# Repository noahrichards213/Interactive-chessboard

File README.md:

# Interactive chessboard

LED-Guided Smart Chessboard
An interactive, LED-guided smart chessboard designed for beginners. The board uses magnetic piece tracking via Hall effect sensors and provides real-time visual move guidance through an integrated LED matrix, all run by an ESP32.

# How it works:
All the chess pieces have small magnets taped on the bottom
On each square of the chessboard, there is a Hall effect sensor, which detects if a square is occupied or empty. 
So, we  calculate piece movement by polling the Hall effects twice:
1. If a Hall effect has changed from detecting something to not detecting something, then a piece has been lifted up
2. Then, if a Hall effect has changed from not detecting something to detecting something, then that piece has been placed down

As such, we have information about the location of all the pieces on the board on every move, which is stored in an 8x8 array.
From there, we iterate over every piece and run an algorithm to update its legal moves. These algorithms take advantage of the geometry of the chessboard. For example, a rook can move horizontally and vertically, so the algorithm to check rook moves checks elements in the array that are in the same row or column. 

Each square on the board is assigned a number, and the available moves of each piece are stored in an array containing these numbers. The number uniquely encodes information about the row and column of the square. The array exists as a field in the Piece object.

The numbers in that array are mapped to a 64-bit binary number that indicates which LED should be lit up. 
For example, the number 25 corresponds to the square with row 2 and column 5 (0-indexed). Each shift register controls the LEDS in a particular row, so the number 2 indicates which register ought to receive data, and the number 5 indicates which of the pins on that shift register ought to receive data. The data in question is the bit 0. The pins of the shift register are connected to the negative terminal of the LEDs. Since the positive end of the LED is always powered, upon receiving a bit 0, the LED is grounded and will light up. Otherwise, the LED is not connected and will not light up.

We iterate this algorithm over all the available moves for a piece that has been lifted up, so the player can see which moves exist in the position.
Upon checkmate, a similar algorithm is used to light up:
1. the checkmated king
2. the enemy pieces that contributed to the checkmate

Video of the Scholar's mate:

https://github.com/user-attachments/assets/231e7ca0-4020-4f57-ace3-88c942b9550d

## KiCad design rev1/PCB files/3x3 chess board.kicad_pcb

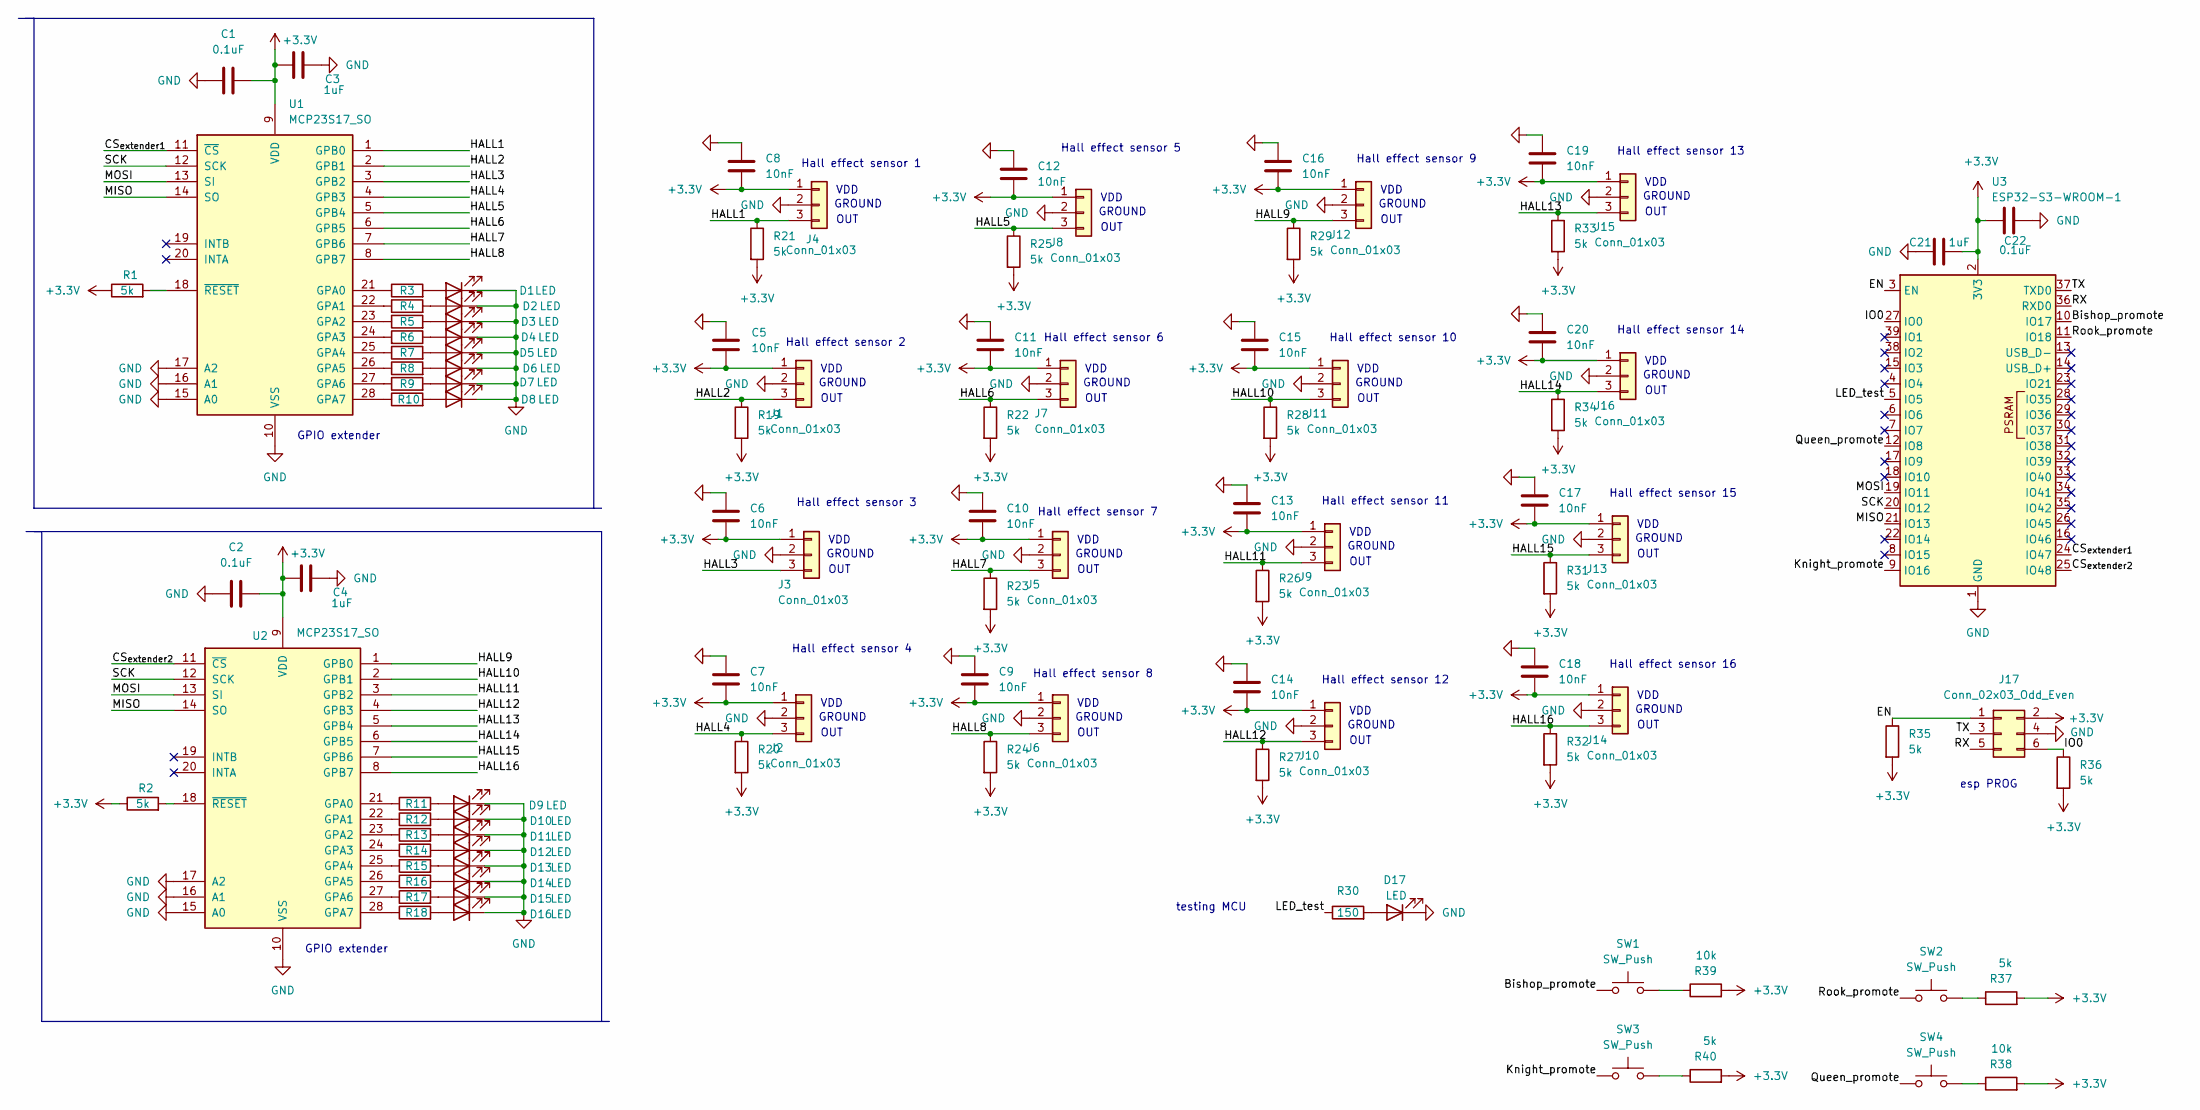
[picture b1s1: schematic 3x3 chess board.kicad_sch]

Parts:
C1, C2, C22: 0.1uF; C_0805_2012Metric
C3, C4, C21: 1uF; C_0805_2012Metric
C5, C6, C7, C8, C9, C10, C11, C12, C13, C14, C15, C16, C17, C18, C19, C20: 10nF; C_0805_2012Metric
D1, D2, D3, D4, D5, D6, D7, D8, D9, D10, D11, D12, D13, D14, D15, D16, D17: LED; D_0805_2012Metric_Pad1.15x1.40mm_HandSolder
J1, J2, J3, J4, J5, J6, J7, J8, J9, J10, J11, J12, J13, J14, J15, J16: Conn_01x03; TSOT-3L_MLX92232LSE-AAA-002-SP_MEL
J17: Conn_02x03_Odd_Even; IDC-Header_2x03_P2.54mm_Vertical
R1, R2, R19, R20, R21, R22, R23, R24, R25, R26, R27, R28, R29, R31, R32, R33, R34, R35, R36, R37, R40: 5k; R_0805_2012Metric_Pad1.20x1.40mm_HandSolder
R3, R4, R5, R6, R7, R8, R9, R10, R11, R12, R13, R14, R15, R16, R17, R18, R30: 150; R_0805_2012Metric_Pad1.20x1.40mm_HandSolder
R38, R39: 10k; R_0805_2012Metric_Pad1.20x1.40mm_HandSolder
SW1, SW2, SW3, SW4: SW_Push; SW_PUSH_6mm_H4.3mm
U1, U2: MCP23S17_SO; SOIC-28W_7.5x17.9mm_P1.27mm
U3: ESP32-S3-WROOM-1

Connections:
+3.3V: C1.2, C2.2, C3.2, C4.2, C5.2, C6.2, C7.2, C8.2, C9.2, C10.2, C11.2, C12.2, C13.2, C14.2, C15.2, C16.2, C17.2, C18.2, C19.2, C20.2, C21.2, C22.2, J1.1, J2.1, J3.1, J4.1, J5.1, J6.1, J7.1, J8.1, J9.1, J10.1, J11.1, J12.1, J13.1, J14.1, J15.1, J16.1, J17.2, R1.1, R2.1, R19.2, R20.2, R21.2, R22.2, R23.2, R24.2, R25.2, R26.2, R27.2, R28.2, R29.2, R31.2, R32.2, R33.2, R34.2, R35.2, R36.2, R37.2, R38.2, R39.2, R40.2, U1.9 (VDD), U2.9 (VDD), U3.2 (3V3)
/Bishop_promote: SW1.1, U3.10 (IO17)
/CS_{extender1}: U1.11 (~CS), U3.24 (IO47)
/CS_{extender2}: U2.11 (~CS), U3.25 (IO48)
/EN: J17.1, R35.1, U3.3 (EN)
/HALL1: J4.3, R21.1, U1.1 (GPB0)
/HALL2: J1.3, R19.1, U1.2 (GPB1)
/HALL3: J3.3, U1.3 (GPB2)
/HALL4: J2.3, R20.1, U1.4 (GPB3)
/HALL5: J8.3, R25.1, U1.5 (GPB4)
/HALL6: J7.3, R22.1, U1.6 (GPB5)
/HALL7: J5.3, R23.1, U1.7 (GPB6)
/HALL8: J6.3, R24.1, U1.8 (GPB7)
/HALL9: J12.3, R29.1, U2.1 (GPB0)
/HALL10: J11.3, R28.1, U2.2 (GPB1)
/HALL11: J9.3, R26.1, U2.3 (GPB2)
/HALL12: J10.3, R27.1, U2.4 (GPB3)
/HALL13: J15.3, R33.1, U2.5 (GPB4)
/HALL14: J16.3, R34.1, U2.6 (GPB5)
/HALL15: J13.3, R31.1, U2.7 (GPB6)
/HALL16: J14.3, R32.1, U2.8 (GPB7)
/IO0: J17.6, R36.1, U3.27 (IO0)
/Knight_promote: SW3.1, U3.9 (IO16)
/LED_test: R30.1, U3.5 (IO5)
/MISO: U1.14 (SO), U2.14 (SO), U3.21 (IO13)
/MOSI: U1.13 (SI), U2.13 (SI), U3.19 (IO11)
/Queen_promote: SW4.1, U3.12 (IO8)
/RX: J17.5, U3.36 (RXD0)
/Rook_promote: SW2.1, U3.11 (IO18)
/SCK: U1.12 (SCK), U2.12 (SCK), U3.20 (IO12)
/TX: J17.3, U3.37 (TXD0)
GND: C1.1, C2.1, C3.1, C4.1, C5.1, C6.1, C7.1, C8.1, C9.1, C10.1, C11.1, C12.1, C13.1, C14.1, C15.1, C16.1, C17.1, C18.1, C19.1, C20.1, C21.1, C22.1, D1.1 (K), D2.1 (K), D3.1 (K), D4.1 (K), D5.1 (K), D6.1 (K), D7.1 (K), D8.1 (K), D9.1 (K), D10.1 (K), D11.1 (K), D12.1 (K), D13.1 (K), D14.1 (K), D15.1 (K), D16.1 (K), D17.1 (K), J1.2, J2.2, J3.2, J4.2, J5.2, J6.2, J7.2, J8.2, J9.2, J10.2, J11.2, J12.2, J13.2, J14.2, J15.2, J16.2, J17.4, U1.10 (VSS), U1.15 (A0), U1.16 (A1), U1.17 (A2), U2.10 (VSS), U2.15 (A0), U2.16 (A1), U2.17 (A2), U3.1 (GND), U3.40 (GND), U3.41 (GND)
unnamed: D1.2 (A), R3.2
unnamed: D2.2 (A), R4.2
unnamed: D3.2 (A), R5.2
unnamed: D4.2 (A), R6.1
unnamed: D5.2 (A), R7.2
unnamed: D6.2 (A), R8.2
unnamed: D7.2 (A), R9.2
unnamed: D8.2 (A), R10.2
unnamed: D9.2 (A), R11.2
unnamed: D10.2 (A), R12.2
unnamed: D11.2 (A), R13.2
unnamed: D12.2 (A), R14.2
unnamed: D13.2 (A), R15.2
unnamed: D14.2 (A), R16.2
unnamed: D15.2 (A), R17.2
unnamed: D16.2 (A), R18.2
unnamed: D17.2 (A), R30.2
unnamed: R37.1, SW2.2
unnamed: R38.1, SW4.2
unnamed: R39.1, SW1.2
unnamed: R40.1, SW3.2
unnamed: R3.1, U1.21 (GPA0)
unnamed: R4.1, U1.22 (GPA1)
unnamed: R5.1, U1.23 (GPA2)
unnamed: R6.2, U1.24 (GPA3)
unnamed: R7.1, U1.25 (GPA4)
unnamed: R8.1, U1.26 (GPA5)
unnamed: R9.1, U1.27 (GPA6)
unnamed: R10.1, U1.28 (GPA7)
unnamed: R1.2, U1.18 (~RESET)
unnamed: R11.1, U2.21 (GPA0)
unnamed: R12.1, U2.22 (GPA1)
unnamed: R13.1, U2.23 (GPA2)
unnamed: R14.1, U2.24 (GPA3)
unnamed: R15.1, U2.25 (GPA4)
unnamed: R16.1, U2.26 (GPA5)
unnamed: R17.1, U2.27 (GPA6)
unnamed: R18.1, U2.28 (GPA7)
unnamed: R2.2, U2.18 (~RESET)

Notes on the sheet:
GROUND
testing MCU
VDD
Hall effect sensor 6
OUT
GPIO extender
Hall effect sensor 7
Hall effect sensor 15
Hall effect sensor 5
Hall effect sensor 10
esp PROG
Hall effect sensor 13
Hall effect sensor 11
Hall effect sensor 14
Hall effect sensor 16
Hall effect sensor 12
Hall effect sensor 3
Hall effect sensor 1
Hall effect sensor 9
Hall effect sensor 4
Hall effect sensor 8
Hall effect sensor 2

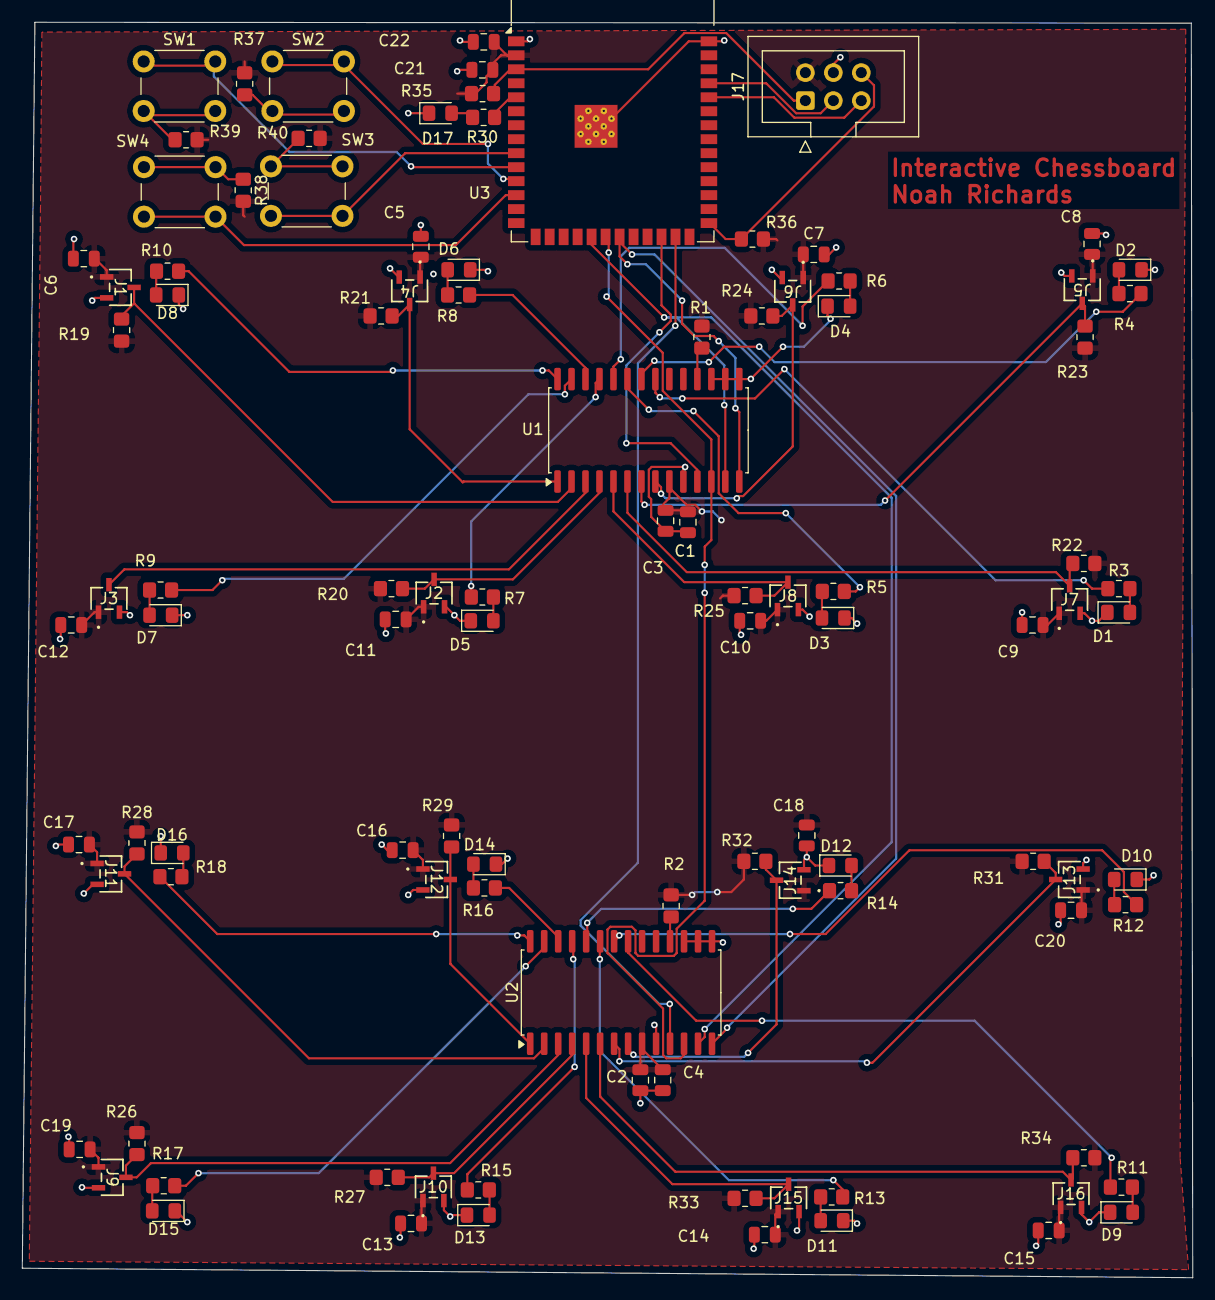
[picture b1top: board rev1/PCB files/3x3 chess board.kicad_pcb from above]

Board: 2 copper layers, 106.3 x 114.0 mm, 103 parts (0 on the bottom side), 71 nets.

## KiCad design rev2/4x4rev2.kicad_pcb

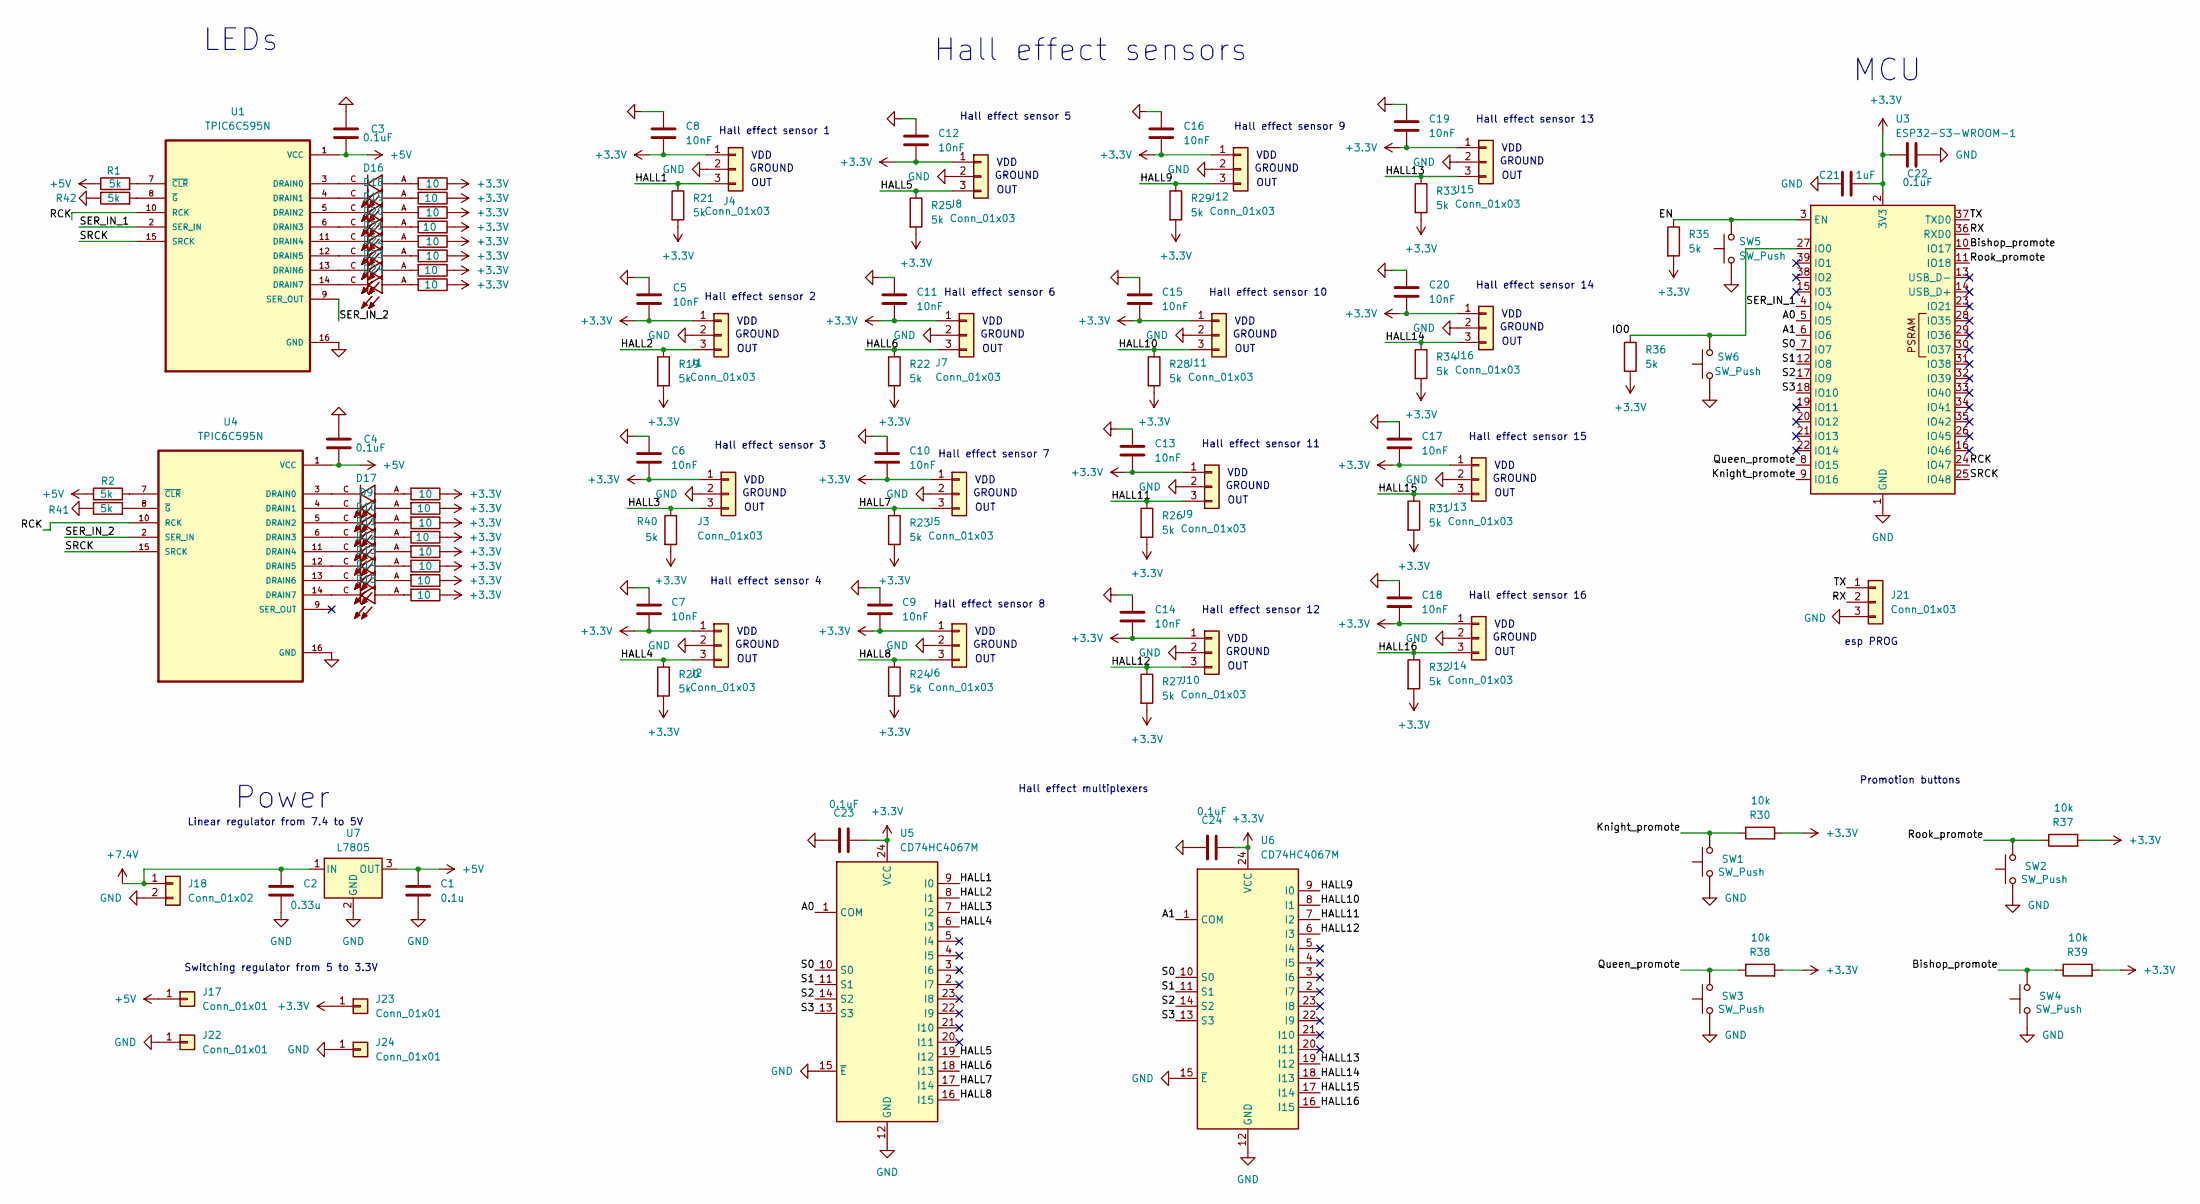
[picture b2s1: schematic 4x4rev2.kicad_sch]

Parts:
C1: 0.1u; C_0805_2012Metric
C2: 0.33u; C_0805_2012Metric
C3, C4, C22, C23, C24: 0.1uF; C_0805_2012Metric
C5, C6, C7, C8, C9, C10, C11, C12, C13, C14, C15, C16, C17, C18, C19, C20: 10nF; C_0805_2012Metric
C21: 1uF; C_0805_2012Metric
D9, D10, D11, D12, D13, D14, D15, D16, D17, D18, D19, D20, D21, D22, D23, D24: JB5630AWT-P-H40GA0000-NZ000001; LED_JB5630AWT-P-H40GA0000-NZ000001; PARTREV 3
J1, J2, J3, J4, J5, J6, J7, J8, J9, J10, J11, J12, J13, J14, J15, J16: Conn_01x03; TSOT-3L_MLX92232LSE-AAA-002-SP_MEL
J17, J22, J23, J24: Conn_01x01; PinHeader_1x01_P2.54mm_Vertical
J18: Conn_01x02; AMASS_XT30U-M_1x02_P5.0mm_Vertical
J21: Conn_01x03; PinHeader_1x03_P2.54mm_Vertical
R1, R2, R19, R20, R21, R22, R23, R24, R25, R26, R27, R28, R29, R31, R32, R33, R34, R35, R36, R40, R41, R42: 5k; R_0805_2012Metric_Pad1.20x1.40mm_HandSolder
R3, R4, R5, R6, R7, R8, R9, R10, R11, R12, R13, R14, R15, R16, R17, R18: 10; R_0805_2012Metric_Pad1.20x1.40mm_HandSolder
R30, R37, R38, R39: 10k; R_0805_2012Metric_Pad1.20x1.40mm_HandSolder
SW1, SW2, SW3, SW4, SW5, SW6: SW_Push; SW_SPST_SKQG_WithStem
U1, U4: TPIC6C595N; SOIC127P600X175-16N
U3: ESP32-S3-WROOM-1
U5, U6: CD74HC4067M; SOIC127P1030X265-24N
U7: L7805; L7805CDTTR

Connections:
+3.3V: C5.2, C6.2, C7.2, C8.2, C9.2, C10.2, C11.2, C12.2, C13.2, C14.2, C15.2, C16.2, C17.2, C18.2, C19.2, C20.2, C21.2, C22.2, C23.2, C24.2, J1.1, J2.1, J3.1, J4.1, J5.1, J6.1, J7.1, J8.1, J9.1, J10.1, J11.1, J12.1, J13.1, J14.1, J15.1, J16.1, J23.1, R3.1, R4.1, R5.1, R6.1, R7.1, R8.1, R9.1, R10.1, R11.1, R12.1, R13.1, R14.1, R15.1, R16.1, R17.1, R18.1, R19.2, R20.2, R21.2, R22.2, R23.2, R24.2, R25.2, R26.2, R27.2, R28.2, R29.2, R30.2, R31.2, R32.2, R33.2, R34.2, R35.2, R36.2, R37.2, R38.2, R39.2, R40.2, U3.2 (3V3), U5.24 (VCC), U6.24 (VCC)
+5V: C1.1, C3.2, C4.2, J17.1, R1.1, R2.1, U1.1 (VCC), U4.1 (VCC), U7.3 (OUT)
+7.4V: C2.1, J18.1, U7.1 (IN)
/A0: U3.5 (IO5), U5.1 (COM)
/A1: U3.6 (IO6), U6.1 (COM)
/Bishop_promote: R39.1, SW4.2, U3.10 (IO17)
/EN: R35.1, SW5.2, U3.3 (EN)
/HALL1: J4.3, R21.1, U5.9 (I0)
/HALL2: J1.3, R19.1, U5.8 (I1)
/HALL3: J3.3, R40.1, U5.7 (I2)
/HALL4: J2.3, R20.1, U5.6 (I3)
/HALL5: J8.3, R25.1, U5.19 (I12)
/HALL6: J7.3, R22.1, U5.18 (I13)
/HALL7: J5.3, R23.1, U5.17 (I14)
/HALL8: J6.3, R24.1, U5.16 (I15)
/HALL9: J12.3, R29.1, U6.9 (I0)
/HALL10: J11.3, R28.1, U6.8 (I1)
/HALL11: J9.3, R26.1, U6.7 (I2)
/HALL12: J10.3, R27.1, U6.6 (I3)
/HALL13: J15.3, R33.1, U6.19 (I12)
/HALL14: J16.3, R34.1, U6.18 (I13)
/HALL15: J13.3, R31.1, U6.17 (I14)
/HALL16: J14.3, R32.1, U6.16 (I15)
/IO0: R36.1, SW6.2, U3.27 (IO0)
/Knight_promote: R30.1, SW1.2, U3.9 (IO16)
/Queen_promote: R38.1, SW3.2, U3.8 (IO15)
/RCK: U1.10 (RCK), U3.24 (IO47), U4.10 (RCK)
/RX: J21.2, U3.36 (RXD0)
/Rook_promote: R37.1, SW2.2, U3.11 (IO18)
/S0: U3.7 (IO7), U5.10 (S0), U6.10 (S0)
/S1: U3.12 (IO8), U5.11 (S1), U6.11 (S1)
/S2: U3.17 (IO9), U5.14 (S2), U6.14 (S2)
/S3: U3.18 (IO10), U5.13 (S3), U6.13 (S3)
/SER_IN_1: U1.2 (SER_IN), U3.4 (IO4)
/SER_IN_2: U1.9 (SER_OUT), U4.2 (SER_IN)
/SRCK: U1.15 (SRCK), U3.25 (IO48), U4.15 (SRCK)
/TX: J21.1, U3.37 (TXD0)
GND: C1.2, C2.2, C3.1, C4.1, C5.1, C6.1, C7.1, C8.1, C9.1, C10.1, C11.1, C12.1, C13.1, C14.1, C15.1, C16.1, C17.1, C18.1, C19.1, C20.1, C21.1, C22.1, C23.1, C24.1, J1.2, J2.2, J3.2, J4.2, J5.2, J6.2, J7.2, J8.2, J9.2, J10.2, J11.2, J12.2, J13.2, J14.2, J15.2, J16.2, J18.2, J21.3, J22.1, J24.1, R41.1, R42.1, SW1.1, SW2.1, SW3.1, SW4.1, SW5.1, SW6.1, U1.16 (GND), U3.1 (GND), U3.40 (GND), U3.41 (GND), U4.16 (GND), U5.12 (GND), U5.15 (~E), U6.12 (GND), U6.15 (~E), U7.2 (GND)
unnamed: D9.A, R12.2
unnamed: D10.A, R13.2
unnamed: D11.A, R14.2
unnamed: D12.A, R15.2
unnamed: D13.A, R16.2
unnamed: D14.A, R17.2
unnamed: D15.A, R18.2
unnamed: D16.A, R3.2
unnamed: D17.A, R11.2
unnamed: D18.A, R4.2
unnamed: D19.A, R5.2
unnamed: D20.A, R6.2
unnamed: D21.A, R7.2
unnamed: D22.A, R8.2
unnamed: D23.A, R9.2
unnamed: D24.A, R10.2
unnamed: D16.C, U1.3 (DRAIN0)
unnamed: D18.C, U1.4 (DRAIN1)
unnamed: D19.C, U1.5 (DRAIN2)
unnamed: D20.C, U1.6 (DRAIN3)
unnamed: D21.C, U1.11 (DRAIN4)
unnamed: D22.C, U1.12 (DRAIN5)
unnamed: D23.C, U1.13 (DRAIN6)
unnamed: D24.C, U1.14 (DRAIN7)
unnamed: R1.2, U1.7 (~CLR)
unnamed: R42.2, U1.8 (~G)
unnamed: D17.C, U4.3 (DRAIN0)
unnamed: D9.C, U4.4 (DRAIN1)
unnamed: D10.C, U4.5 (DRAIN2)
unnamed: D11.C, U4.6 (DRAIN3)
unnamed: D12.C, U4.11 (DRAIN4)
unnamed: D13.C, U4.12 (DRAIN5)
unnamed: D14.C, U4.13 (DRAIN6)
unnamed: D15.C, U4.14 (DRAIN7)
unnamed: R2.2, U4.7 (~CLR)
unnamed: R41.2, U4.8 (~G)

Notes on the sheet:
OUT
esp PROG
GROUND
VDD
Hall effect sensor 10
Hall effect sensor 9
Power
Hall effect sensor 15
Hall effect sensor 1
Promotion buttons
Hall effect sensor 14
Hall effect sensor 5
Hall effect sensor 16
Hall effect sensor 2
Hall effect sensor 3
LEDs
Hall effect sensor 8
Hall effect multiplexers
Hall effect sensor 11
Linear regulator from 7.4 to 5V
Switching regulator from 5 to 3.3V
MCU
Hall effect sensor 4
Hall effect sensor 7
Hall effect sensors
Hall effect sensor 13
Hall effect sensor 12
Hall effect sensor 6

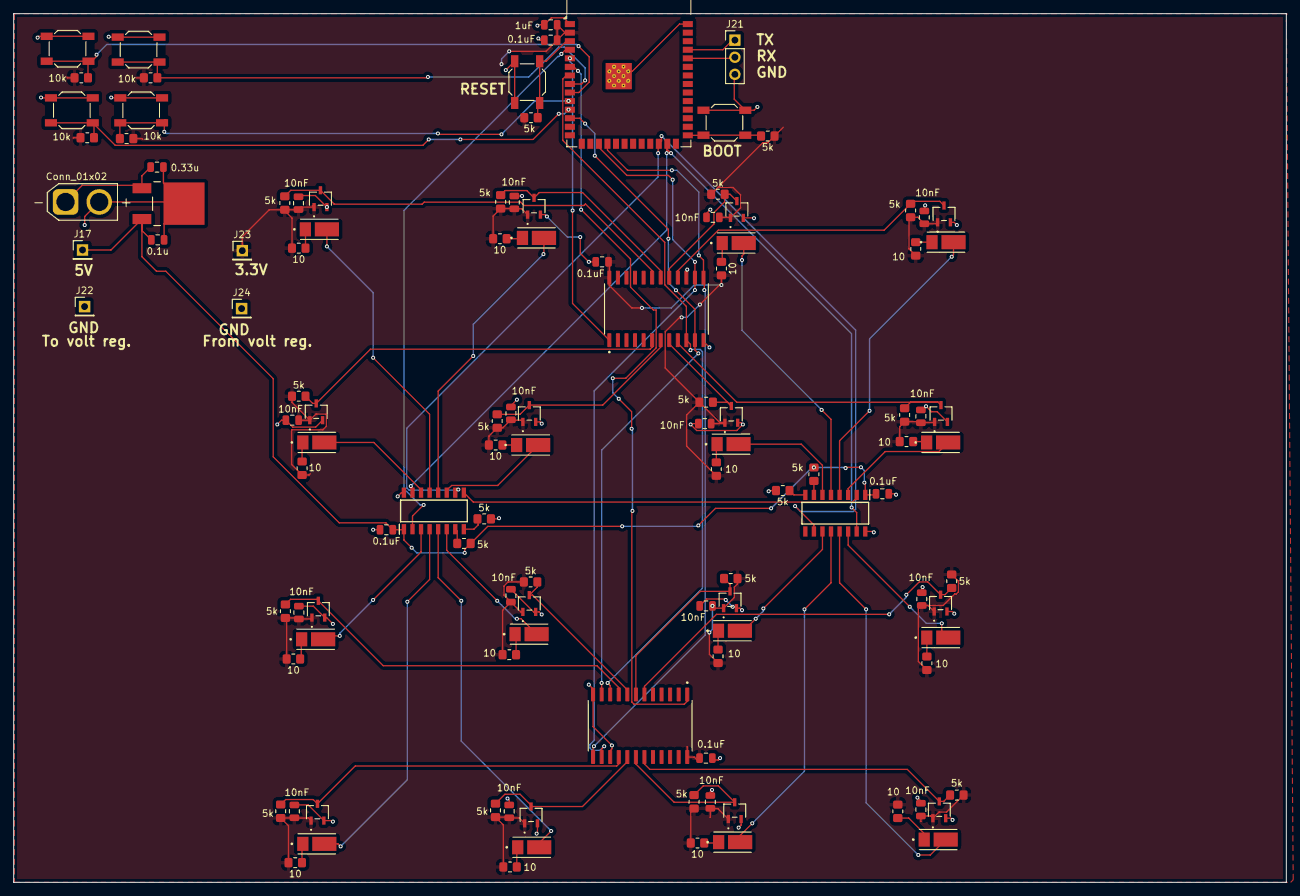
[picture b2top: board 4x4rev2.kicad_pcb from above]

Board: 2 copper layers, 188.8 x 128.9 mm, 116 parts (0 on the bottom side), 74 nets.

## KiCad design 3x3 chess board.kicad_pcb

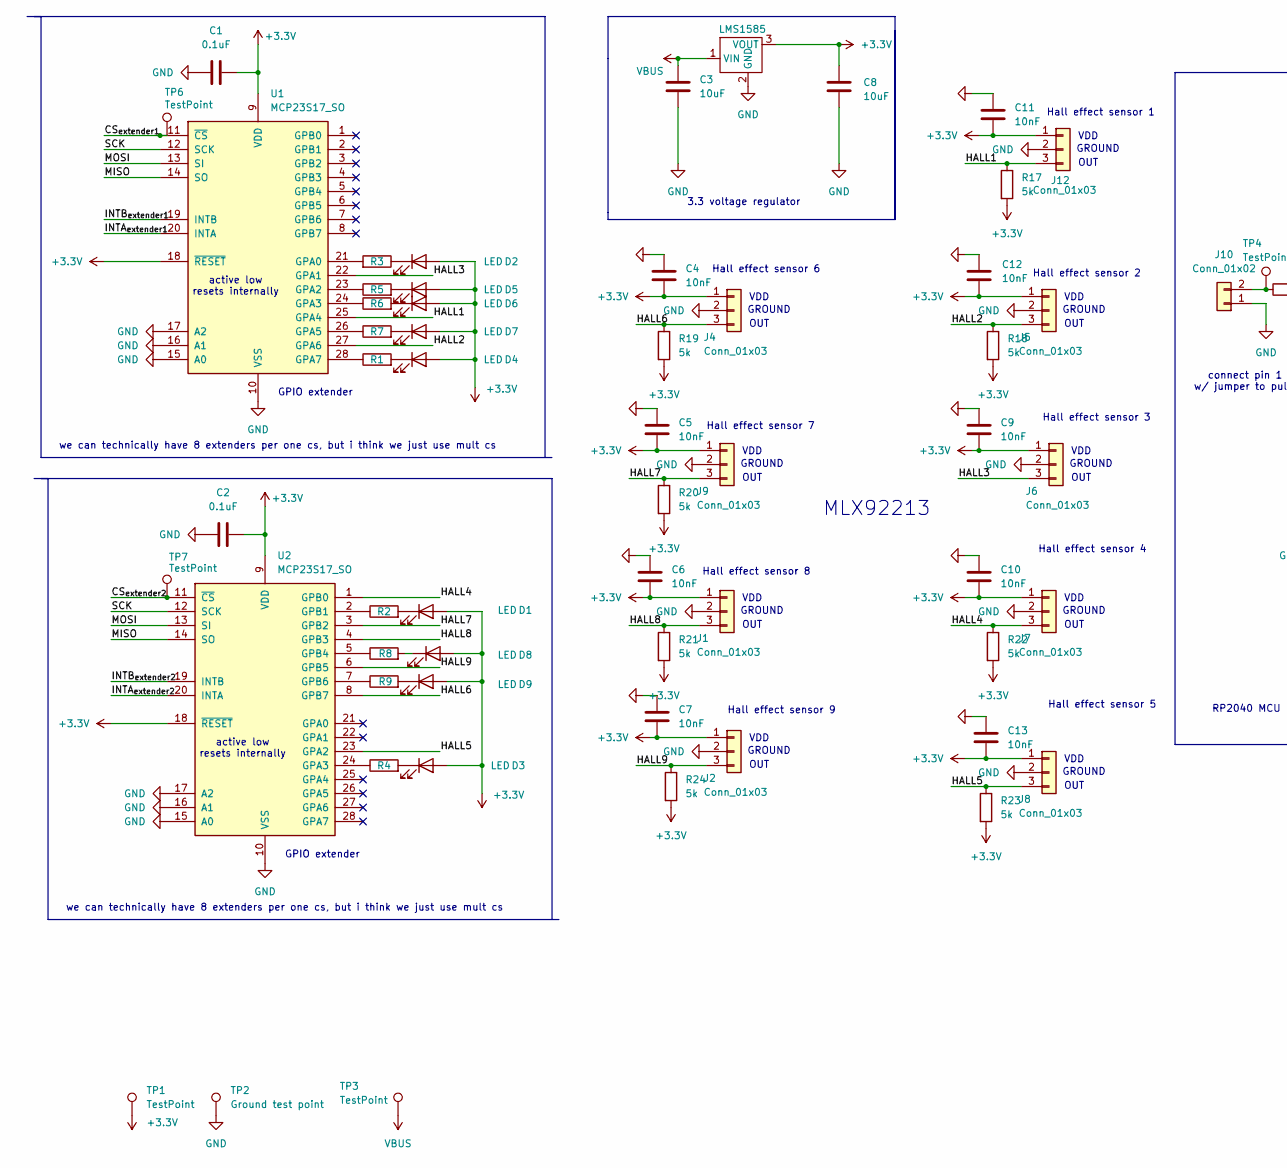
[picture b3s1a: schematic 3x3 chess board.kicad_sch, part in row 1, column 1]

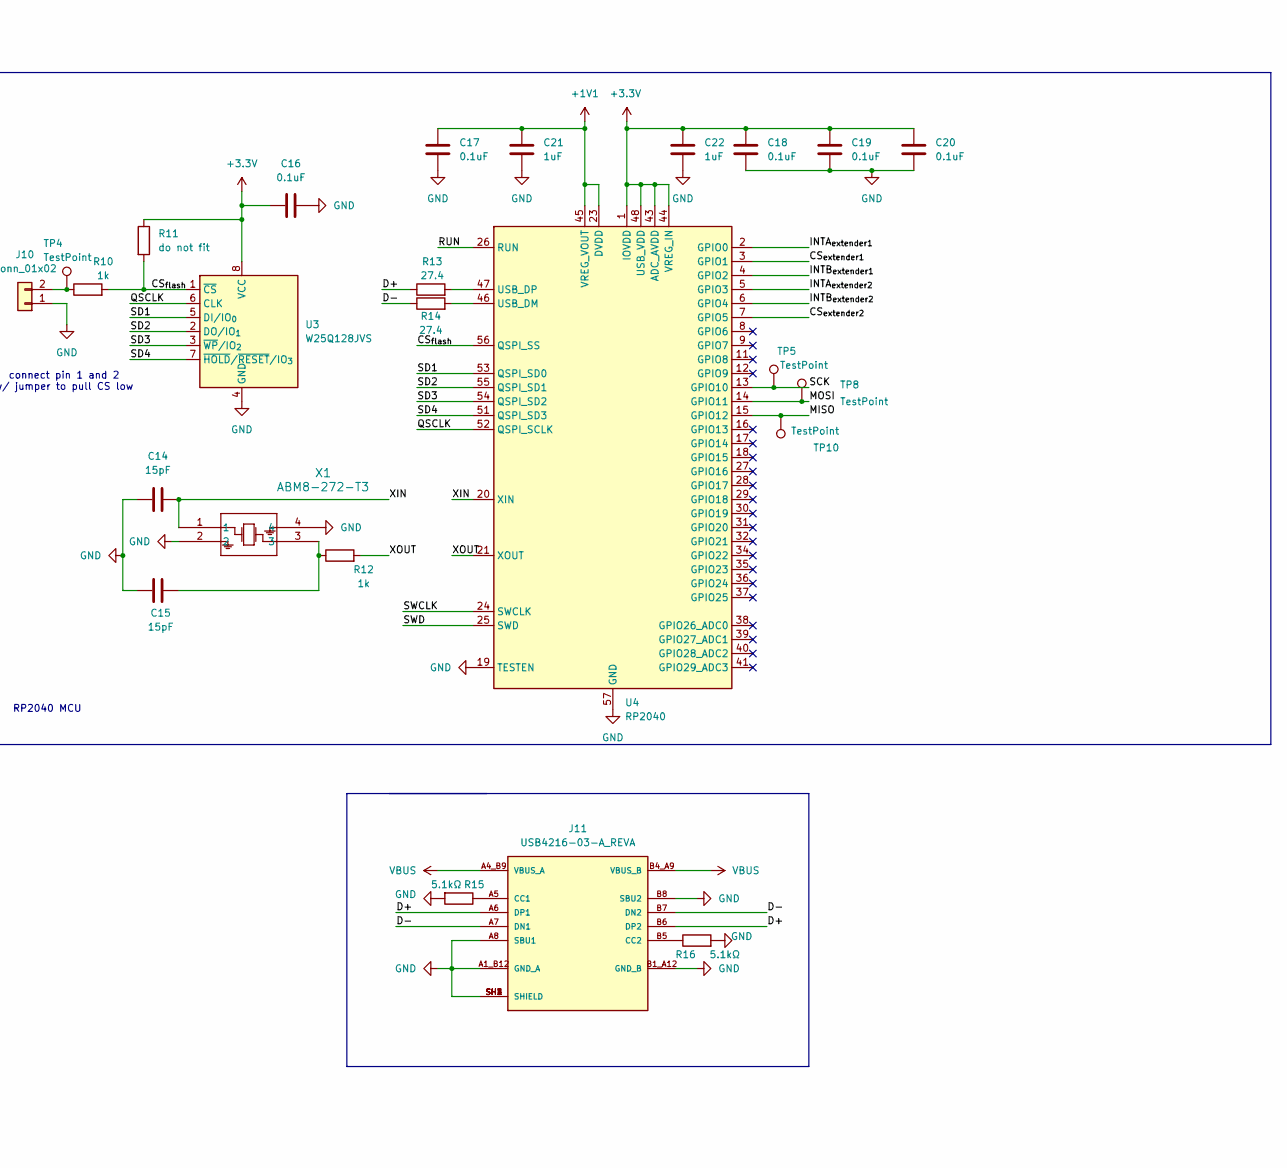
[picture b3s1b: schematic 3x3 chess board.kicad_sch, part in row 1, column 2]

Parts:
C1, C2, C16, C17, C18, C19, C20: 0.1uF; C_0805_2012Metric
C3, C8: 10uF; C_0805_2012Metric
C4, C5, C6, C7, C9, C10, C11, C12, C13: 10nF; C_0805_2012Metric
C14, C15: 15pF; C_0805_2012Metric
C21, C22: 1uF; C_0805_2012Metric_Pad1.18x1.45mm_HandSolder
D1, D2, D3, D4, D5, D6, D7, D8, D9: LED; D_0805_2012Metric_Pad1.15x1.40mm_HandSolder
J1, J2, J4, J5, J6, J7, J8, J9, J12: Conn_01x03; TSOT-3L_MLX92232LSE-AAA-002-SP_MEL
J10: Conn_01x02; PinHeader_1x02_P2.54mm_Vertical
J11: USB4216-03-A_REVA; USB 2.0; PARTREV A
LMS1585: KTT0003B
R1, R2, R3, R4, R5, R6, R7, R8, R9: 16; R_0805_2012Metric_Pad1.20x1.40mm_HandSolder
R10, R12: 1k; R_0805_2012Metric_Pad1.20x1.40mm_HandSolder
R11: do not fit; R_0805_2012Metric_Pad1.20x1.40mm_HandSolder
R13, R14: 27.4; R_1210_3225Metric_Pad1.30x2.65mm_HandSolder
R15, R16: 5.1kΩ; R_0805_2012Metric_Pad1.20x1.40mm_HandSolder
R17, R18, R19, R20, R21, R22, R23, R24: 5k; R_0805_2012Metric_Pad1.20x1.40mm_HandSolder
TP1, TP3, TP4, TP5, TP6, TP7, TP8, TP10: TestPoint; TestPoint_Pad_2.0x2.0mm
TP2: Ground test point; TestPoint_Pad_2.0x2.0mm
U1, U2: MCP23S17_SO; SOIC-28W_7.5x17.9mm_P1.27mm
U3: W25Q128JVS; SOIC-8_5.3x5.3mm_P1.27mm
U4: RP2040; QFN-56-1EP_7x7mm_P0.4mm_EP3.2x3.2mm
X1: ABM8-272-T3; ABM8-272-T3_ABR

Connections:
+1V1: C17.1, C21.1, U4.23 (DVDD), U4.45 (VREG_VOUT), U4.50 (DVDD)
+3.3V: C1.2, C2.2, C4.2, C5.2, C6.2, C7.2, C8.1, C9.2, C10.2, C11.2, C12.2, C13.2, C16.1, C18.1, C19.1, C20.1, C22.1, D1.2 (A), D2.2 (A), D3.2 (A), D4.2 (A), D5.2 (A), D6.2 (A), D7.2 (A), D8.2 (A), D9.2 (A), J1.1, J2.1, J4.1, J5.1, J6.1, J7.1, J8.1, J9.1, J12.1, LMS1585.3 (VOUT), R11.1, R17.2, R18.2, R19.2, R20.2, R21.2, R22.2, R23.2, R24.2, TP1.1, U1.9 (VDD), U1.18 (~RESET), U2.9 (VDD), U2.18 (~RESET), U3.8 (VCC), U4.1 (IOVDD), U4.10 (IOVDD), U4.22 (IOVDD), U4.33 (IOVDD), U4.42 (IOVDD), U4.43 (ADC_AVDD), U4.44 (VREG_IN), U4.48 (USB_VDD), U4.49 (IOVDD)
/CS_{extender1}: TP6.1, U1.11 (~CS), U4.3 (GPIO1)
/CS_{extender2}: TP7.1, U2.11 (~CS), U4.7 (GPIO5)
/CS_{flash}: R10.2, R11.2, U3.1 (~CS), U4.56 (QSPI_SS)
/D+: J11.A6 (DP1), J11.B6 (DP2), R13.1
/D-: J11.A7 (DN1), J11.B7 (DN2), R14.1
/HALL1: J12.3, R17.1, U1.25 (GPA4)
/HALL2: J5.3, R18.1, U1.27 (GPA6)
/HALL3: J6.3, U1.22 (GPA1)
/HALL4: J7.3, R22.1, U2.1 (GPB0)
/HALL5: J8.3, R23.1, U2.23 (GPA2)
/HALL6: J4.3, R19.1, U2.8 (GPB7)
/HALL7: J9.3, R20.1, U2.3 (GPB2)
/HALL8: J1.3, R21.1, U2.4 (GPB3)
/HALL9: J2.3, R24.1, U2.6 (GPB5)
/INTA_{extender1}: U1.20 (INTA), U4.2 (GPIO0)
/INTA_{extender2}: U2.20 (INTA), U4.5 (GPIO3)
/INTB_{extender1}: U1.19 (INTB), U4.4 (GPIO2)
/INTB_{extender2}: U2.19 (INTB), U4.6 (GPIO4)
/MISO: TP10.1, U1.14 (SO), U2.14 (SO), U4.15 (GPIO12)
/MOSI: TP8.1, U1.13 (SI), U2.13 (SI), U4.14 (GPIO11)
/QSCLK: U3.6 (CLK), U4.52 (QSPI_SCLK)
/RUN: U4.26 (RUN)
/SCK: TP5.1, U1.12 (SCK), U2.12 (SCK), U4.13 (GPIO10)
/SD1: U3.5 (DI/IO_{0}), U4.53 (QSPI_SD0)
/SD2: U3.2 (DO/IO_{1}), U4.55 (QSPI_SD1)
/SD3: U3.3 (~WP/IO_{2}), U4.54 (QSPI_SD2)
/SD4: U3.7 (~HOLD/~RESET/IO_{3}), U4.51 (QSPI_SD3)
/SWCLK: U4.24 (SWCLK)
/SWD: U4.25 (SWD)
/XIN: C14.2, U4.20 (XIN), X1.1
/XOUT: R12.2, U4.21 (XOUT)
GND: C1.1, C2.1, C3.2, C4.1, C5.1, C6.1, C7.1, C8.2, C9.1, C10.1, C11.1, C12.1, C13.1, C14.1, C15.2, C16.2, C17.2, C18.2, C19.2, C20.2, C21.2, C22.2, J1.2, J2.2, J4.2, J5.2, J6.2, J7.2, J8.2, J9.2, J10.1, J11.A1_B12 (GND_A), J11.A8 (SBU1), J11.B1_A12 (GND_B), J11.B8 (SBU2), J11.SH1 (SHIELD), J11.SH2 (SHIELD), J11.SH3 (SHIELD), J11.SH4 (SHIELD), J12.2, LMS1585.2 (GND), R15.2, R16.2, TP2.1, U1.10 (VSS), U1.15 (A0), U1.16 (A1), U1.17 (A2), U2.10 (VSS), U2.15 (A0), U2.16 (A1), U2.17 (A2), U3.4 (GND), U4.19 (TESTEN), U4.57 (GND), X1.2, X1.4
unnamed: C15.1, R12.1, X1.3
unnamed: D1.1 (K), R2.2
unnamed: D2.1 (K), R3.1
unnamed: D3.1 (K), R4.2
unnamed: D4.1 (K), R1.2
unnamed: D5.1 (K), R5.2
unnamed: D6.1 (K), R6.2
unnamed: D7.1 (K), R7.2
unnamed: D8.1 (K), R8.2
unnamed: D9.1 (K), R9.2
unnamed: J10.2, R10.1, TP4.1
unnamed: J11.A5 (CC1), R15.1
unnamed: J11.B5 (CC2), R16.1
unnamed: R3.2, U1.21 (GPA0)
unnamed: R5.1, U1.23 (GPA2)
unnamed: R6.1, U1.24 (GPA3)
unnamed: R7.1, U1.26 (GPA5)
unnamed: R1.1, U1.28 (GPA7)
unnamed: R4.1, U2.24 (GPA3)
unnamed: R2.1, U2.2 (GPB1)
unnamed: R8.1, U2.5 (GPB4)
unnamed: R9.1, U2.7 (GPB6)
unnamed: R14.2, U4.46 (USB_DM)
unnamed: R13.2, U4.47 (USB_DP)
VBUS: C3.1, J11.A4_B9 (VBUS_A), J11.B4_A9 (VBUS_B), LMS1585.1 (VIN), TP3.1

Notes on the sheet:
VDD
Hall effect sensor 6
we can technically have 8 extenders per one cs, but i think we just use mult cs
OUT
GPIO extender
GROUND
connect pin 1 and 2 w/ jumper to pull CS low
Hall effect sensor 7
MLX92213
Hall effect sensor 5
3.3 voltage regulator
active low resets internally
Hall effect sensor 3
Hall effect sensor 1
RP2040 MCU
Hall effect sensor 9
Hall effect sensor 4
Hall effect sensor 8
Hall effect sensor 2

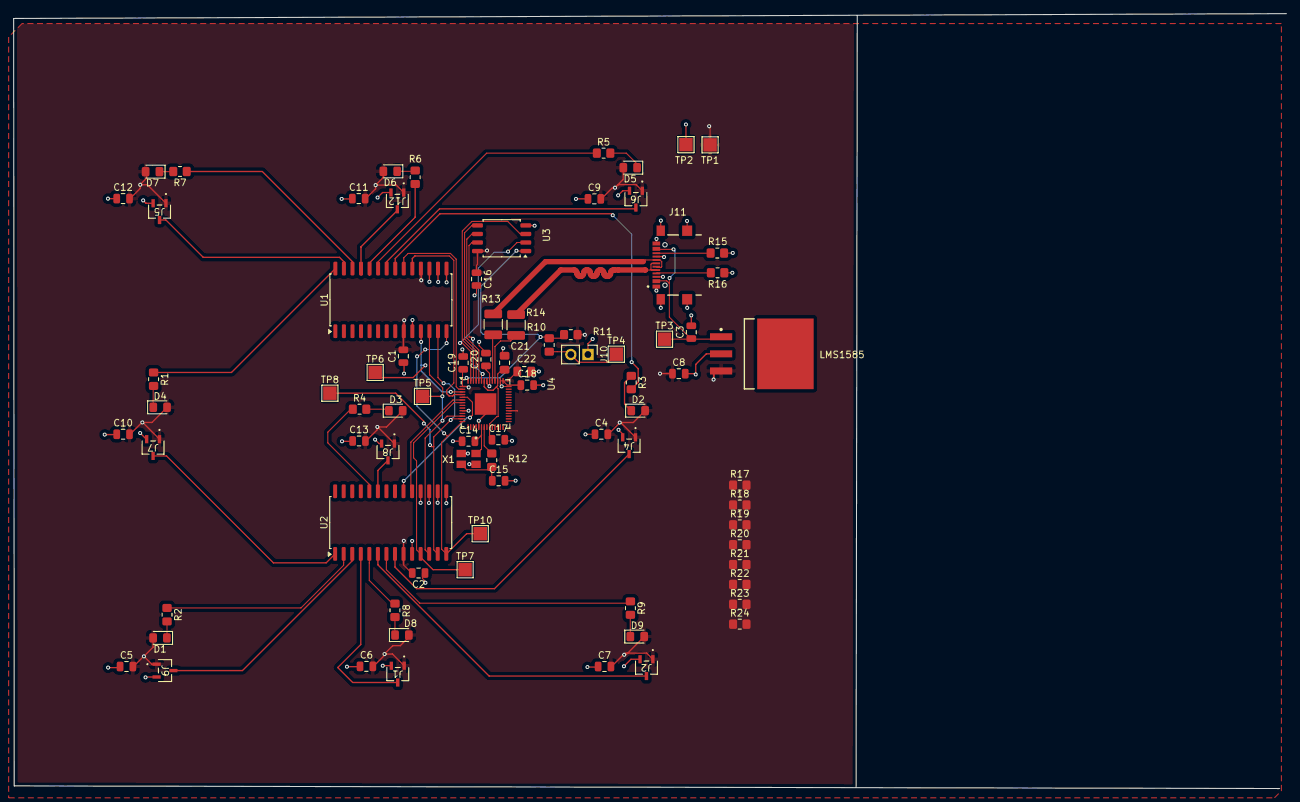
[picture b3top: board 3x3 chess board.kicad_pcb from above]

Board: 2 copper layers, 189.0 x 115.1 mm, 81 parts (0 on the bottom side), 56 nets.

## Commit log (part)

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2026-03-08 adding kicad files
2026-03-08 adding firmware files
2026-03-08 Create PCB files
2026-03-08 Create firmware files
2026-03-08 adding firmware files to folder
2026-03-08 adding PCB files to folder
2026-04-02 update schematic and and pcb w/ new mcu
2026-04-02 update for no drc errors
2026-05-05 Changes
    - updated PCB
    - now pieces can't move such that check is allowed
2026-05-05 changes
    added promotion buttons, removed interrupts, cleaned up silkscreen
2026-05-07 changes
    fixed promotion, verfiied castling, now working on en passant
2026-05-07 changes
    successfully created en passant, fixed castling
2026-05-07 fix
    deleted copy files
2026-05-09 DONE
    fixed yesterday's problem, as far as I am aware, FULLY OPERATIONAL CHESS GAME
2026-05-09 adjustments before ordering
    udpated res values, added gerber files and parts list files
2026-05-09 added 4x4 board
    next step: edit 4x4 board to be ready for testing
2026-05-11 changes
    4x4 code comiples and runs, many errors so far
2026-05-12 changes
    - finished debugging 4x4
    - started on firmware pseudo for picking up and putting pieces structure
2026-05-16 changes
    finished psuedocode for firmware
2026-05-18 revert back to dynamic mem alloc
2026-05-18 Revert "changes"
    This reverts commit b2123568545d61a34555078c56789028945e4b54.
2026-05-18 changes
    started debuggin malloc
2026-05-19 changes
    finished debugging en passant
2026-05-19 changes
    started writing real code for the pseudocode
2026-05-20 changes
    making capture moves negative, updated firmware (needed to account for castling, promotion, en passant now)
2026-05-20 changes
    finished firmware for picking up and placing down pieces logic
2026-05-20 changes
    continuing to integrate main program w/ MCP codde
2026-05-20 changes
    continued progress on firmware
2026-05-29 changes
    finished pseudcode structure for program
2026-06-10 changes
    notes about plan for week of june 8
2026-06-24 update
    catching up notes and extender code
2026-06-25 fixing file bugs
    fixing file bugs
